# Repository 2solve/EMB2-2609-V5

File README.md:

# IC2S Extension Board EBM2 V5 — 6 entradas 4-20 mA

Placa de extensão da família IC2S (2Solve), código **IC2S-EBM2-2609-V5.0**. Seis entradas analógicas de 4-20 mA
para a Universal Baseboard; **substituição directa da EBM2 V4.1** (contorno 60 × 60 mm, furação e pinagem de
`P1`/`P2` congelados). Projecto em **KiCad 10**.

## Estado (2026-09-28)

| Fase | Estado |
|---|---|
| F0/F1 — escopo e planeamento | fechadas |
| F2 — esquemático, diagrama, BOM preliminar, mapa de pinos | **Portão 1 aprovado** (pacote congelado em `Portao1_aprovado_2026-09-25`) |
| F3 — layout | contorno e placement inicial feitos (DRC 0, paridade 0); falta o Portão 3 e o roteamento |

**Alteração posterior ao Portão 1 (2026-09-28)**, trazida da revisão da EBM7 V2.3: ramo único de 24 V (saem F1, D3 e
R3), 100 nF a 50 V fora do 24 V e um só MPN de 1 µF. Detalhe em
`Documentos_…/00-Especificações_Técnicas_…/alteracoes_reuniao_2026-09-28.md` e na folha 2, notas 3, 11, 13 e 14. Também a 28-09: **U5 MCP1824ST (SOT-223) → MCP1824T-3302E/OT (SOT-23-5)**, o mesmo MPN do U4; C10 (entrada) 1 µF → 10 µF 1206, o datasheet pede 1-10 µF
(`alteracao_LDO_3V3_lado_PLC_2026-09-28.md`). O
pacote congelado do Portão 1 não foi tocado; a BOM preliminar foi regenerada (42 linhas, 123 peças montadas).

## Organização (modelo de pastas de Produtos)

```
Desenvolvimento_IC2S-EBM2-2609-V5.0/
  Arquivos_Fabricação_IC2S-EBM2-2609-V5.0/
    00-Gerbers_…            (vazio até à F3)
    01-BOM_List_…           BOM preliminar (.md/.csv) e respostas cruas da API Mouser (2026-09-25)
    02-Pick-and-Place_…     (vazio até à F3)
    03-Stencil_…            (vazio até à F3)
  Documentos_IC2S-EBM2-2609-V5.0/
    00-Especificações_Técnicas_…   escopo, intenção, planeamento, relatórios, verificações da F2, Portão 1, F3
    01-Esquemáticos_…              PDF de revisão da F2 (esquemático + diagrama + mapa de pinos), PNG e SVG por folha
    02-Pinout_…                    mapa de pinos de P1/P2/U6/U7 e regras para o firmware
    03-Diagrama_Blocos_…           diagrama de blocos (SVG)
  Projeto_IC2S-EBM2-2609-V5.0/
    IC2S_Extension_Board-EBM2_V5.kicad_pro/.kicad_sch/.kicad_pcb e as 7 folhas
    symbols/, footprints/   bibliotecas próprias do projecto (sym-lib-table e fp-lib-table relativas)
    Ferramentas/            scripts Python de geração e verificação (ERC, netlist contra a intenção, BOM, PDF, F3)
    Documentos_de_Referência-IC2S-EBM2-2609-V5.0/   lista dos datasheets usados (nome e md5)
```

## O que não está neste repositório, e porquê

- **Datasheets dos fabricantes**: não se redistribuem num repositório público. `LISTA_datasheets.md` dá o nome e o
  md5 de cada ficheiro usado.
- Backups intermédios (`.antes_*`), netlists e relatórios ERC de passos intermédios, estado local do KiCad
  (`.kicad_prl`, `.history`).
- Ficheiros da V4.1 (Gerbers de origem usados para conferir o contorno): são de outro produto.

## Notas

- Os ficheiros KiCad mantêm o nome `IC2S_Extension_Board-EBM2_V5`: renomear o projecto partiria as instâncias
  dos símbolos nas folhas.
- Referências R1, R2… desde 2026-09-25; uma referência de três dígitos num documento é da numeração antiga
  (tabela em `tabela_correspondencia_refs_EBM2_V5.md`).
- Os scripts em `Ferramentas/` usam os caminhos locais de desenvolvimento (`C:\hw\hw-ebm2-v5`); a consulta à
  Mouser lê a chave de `MOUSER_API_KEY` e nunca a grava.

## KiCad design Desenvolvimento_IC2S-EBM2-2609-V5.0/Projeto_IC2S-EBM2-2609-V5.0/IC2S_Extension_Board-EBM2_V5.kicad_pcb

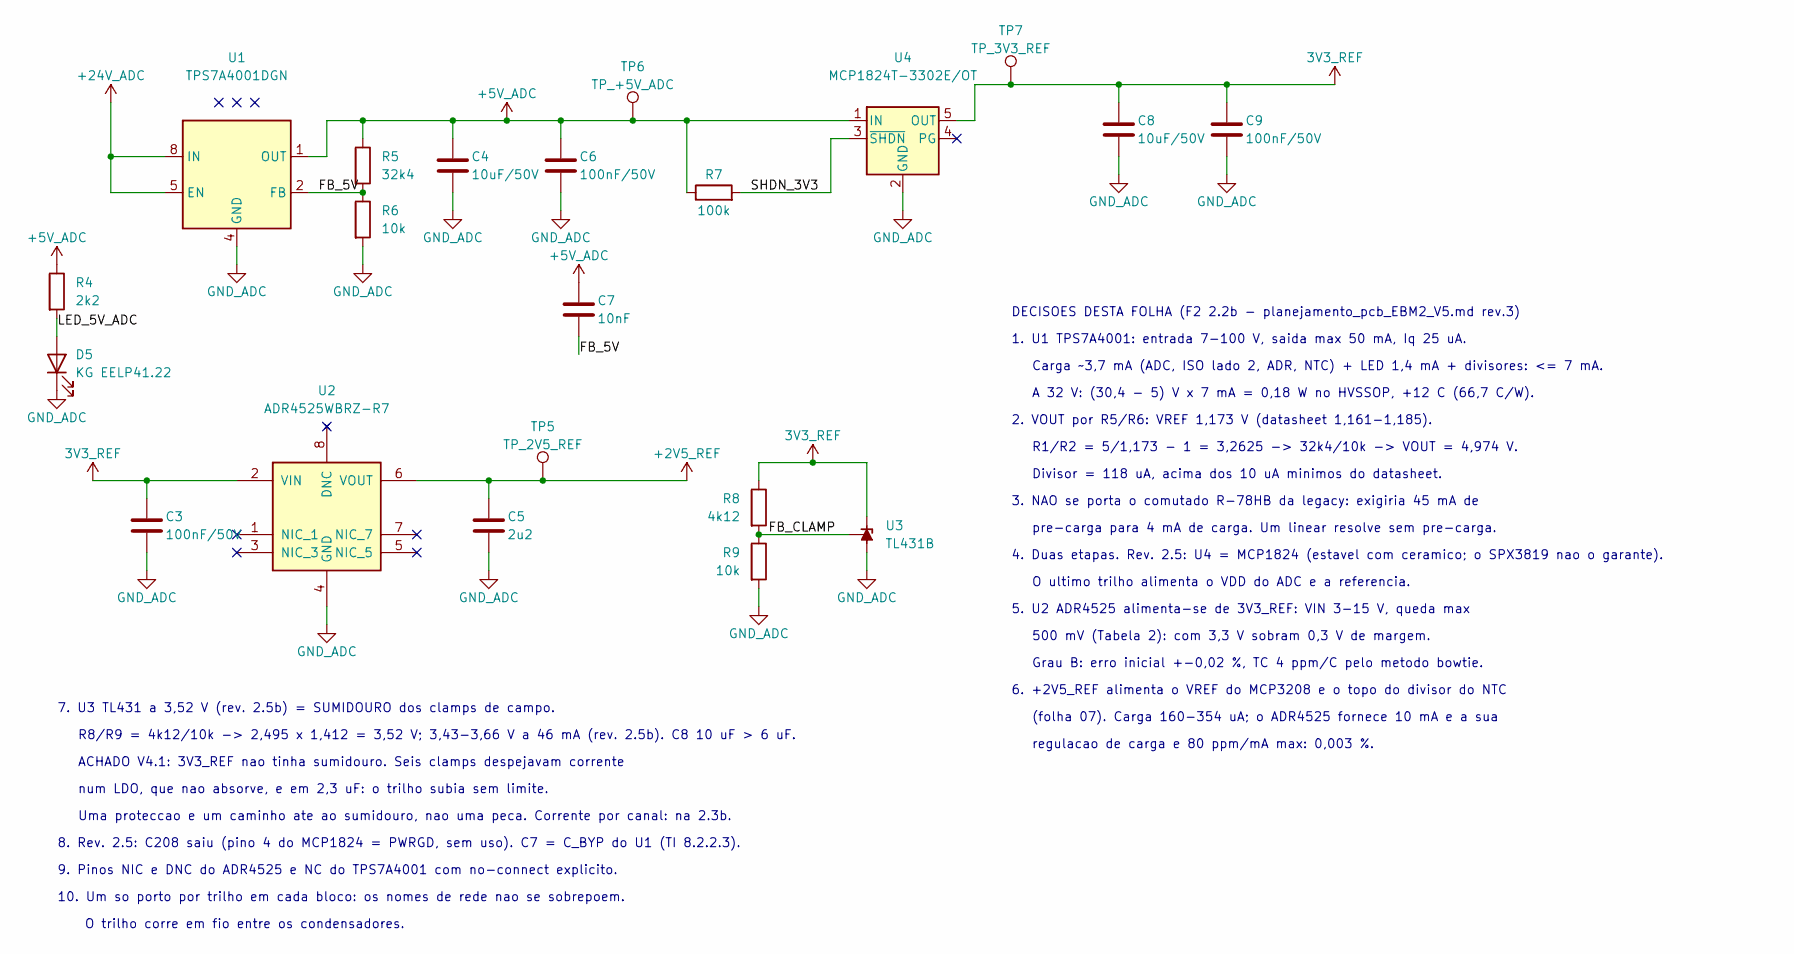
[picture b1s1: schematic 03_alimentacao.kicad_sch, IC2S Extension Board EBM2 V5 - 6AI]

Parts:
C3, C6, C9: 100nF/50V; 0603C; MPN C1608X7R1H104K080AA
C4, C8: 10uF/50V; C_1206_3216Metric; MPN C3216X5R1H106K160AB
C5: 2u2; 0603C; MPN C1608X5R1E225K080AB
C7: 10nF; 0603C; MPN GCM188R71H103KA37J
D5: KG EELP41.22; 0603LED; MPN KG EELP41.22-PHRH-35-A8J8-20-R18
R4: 2k2; 0603R; MPN RC0603FR-072K2L
R5: 32k4; 0603R; MPN RC0603FR-0732K4L
R6, R9: 10k; 0603R; MPN RC0603FR-0710KL
R7: 100k; 0603R; MPN RC0603FR-07100KL
R8: 4k12; 0603R; MPN RC0603FR-074K12L
TP5: TP_2V5_REF; TestPad_Via
TP6: TP_+5V_ADC; TestPad_Via
TP7: TP_3V3_REF; TestPad_Via
U1: TPS7A4001DGN; HVSSOP-8-1EP; MPN TPS7A4001DGNR
U2: ADR4525WBRZ-R7; SOIC8; MPN ADR4525WBRZ-R7
U3: TL431B; SOT23-3; MPN TL431BQDBZR
U4: MCP1824T-3302E/OT; SOT-23-5; MPN MCP1824T-3302E/OT

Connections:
3V3_REF: C3.1, C8.1, C9.1, R8.1, TP7.1, U2.2 (VIN), U3.1 (K), U4.5 (OUT); also elsewhere on the board
+2V5_REF: C5.1, TP5.1, U2.6 (VOUT); also elsewhere on the board
+5V_ADC: C4.1, C6.1, C7.1, R4.1, R5.1, R7.1, TP6.1, U1.1 (OUT), U4.1 (IN)
+24V_ADC: U1.5 (EN), U1.8 (IN); also elsewhere on the board
/3 Alimentacao/FB_5V: C7.2, R5.2, R6.1, U1.2 (FB)
/3 Alimentacao/FB_CLAMP: R8.2, R9.1, U3.2 (REF)
/3 Alimentacao/LED_5V_ADC: D5.2 (A), R4.2
/3 Alimentacao/SHDN_3V3: R7.2, U4.3 (~SHDN)
GND_ADC: C3.2, C4.2, C5.2, C6.2, C8.2, C9.2, D5.1 (K), R6.2, R9.2, U1.4 (GND), U1.9 (PAD), U2.4 (GND), U3.3 (A), U4.2 (GND); also elsewhere on the board

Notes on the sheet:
5. U2 ADR4525 alimenta-se de 3V3_REF: VIN 3-15 V, queda max
R1/R2 = 5/1,173 - 1 = 3,2625 -> 32k4/10k -> VOUT = 4,974 V.
1. U1 TPS7A4001: entrada 7-100 V, saida max 50 mA, Iq 25 uA.
Carga ~3,7 mA (ADC, ISO lado 2, ADR, NTC) + LED 1,4 mA + divisores: <= 7 mA.
Divisor = 118 uA, acima dos 10 uA minimos do datasheet.
10. Um so porto por trilho em cada bloco: os nomes de rede nao se sobrepoem.
7. U3 TL431 a 3,52 V (rev. 2.5b) = SUMIDOURO dos clamps de campo.
A 32 V: (30,4 - 5) V x 7 mA = 0,18 W no HVSSOP, +12 C (66,7 C/W).
regulacao de carga e 80 ppm/mA max: 0,003 %.
4. Duas etapas. Rev. 2.5: U4 = MCP1824 (estavel com ceramico; o SPX3819 nao o garante).
(folha 07). Carga 160-354 uA; o ADR4525 fornece 10 mA e a sua
pre-carga para 4 mA de carga. Um linear resolve sem pre-carga.
num LDO, que nao absorve, e em 2,3 uF: o trilho subia sem limite.
6. +2V5_REF alimenta o VREF do MCP3208 e o topo do divisor do NTC
Grau B: erro inicial +-0,02 %, TC 4 ppm/C pelo metodo bowtie.
O trilho corre em fio entre os condensadores.
Uma proteccao e um caminho ate ao sumidouro, nao uma peca. Corrente por canal: na 2.3b.
9. Pinos NIC e DNC do ADR4525 e NC do TPS7A4001 com no-connect explicito.
ACHADO V4.1: 3V3_REF nao tinha sumidouro. Seis clamps despejavam corrente
3. NAO se porta o comutado R-78HB da legacy: exigiria 45 mA de
R8/R9 = 4k12/10k -> 2,495 x 1,412 = 3,52 V; 3,43-3,66 V a 46 mA (rev. 2.5b). C8 10 uF > 6 uF.
500 mV (Tabela 2): com 3,3 V sobram 0,3 V de margem.
O ultimo trilho alimenta o VDD do ADC e a referencia.
2. VOUT por R5/R6: VREF 1,173 V (datasheet 1,161-1,185).
DECISOES DESTA FOLHA (F2 2.2b - planejamento_pcb_EBM2_V5.md rev.3)
8. Rev. 2.5: C208 saiu (pino 4 do MCP1824 = PWRGD, sem uso). C7 = C_BYP do U1 (TI 8.2.2.3).

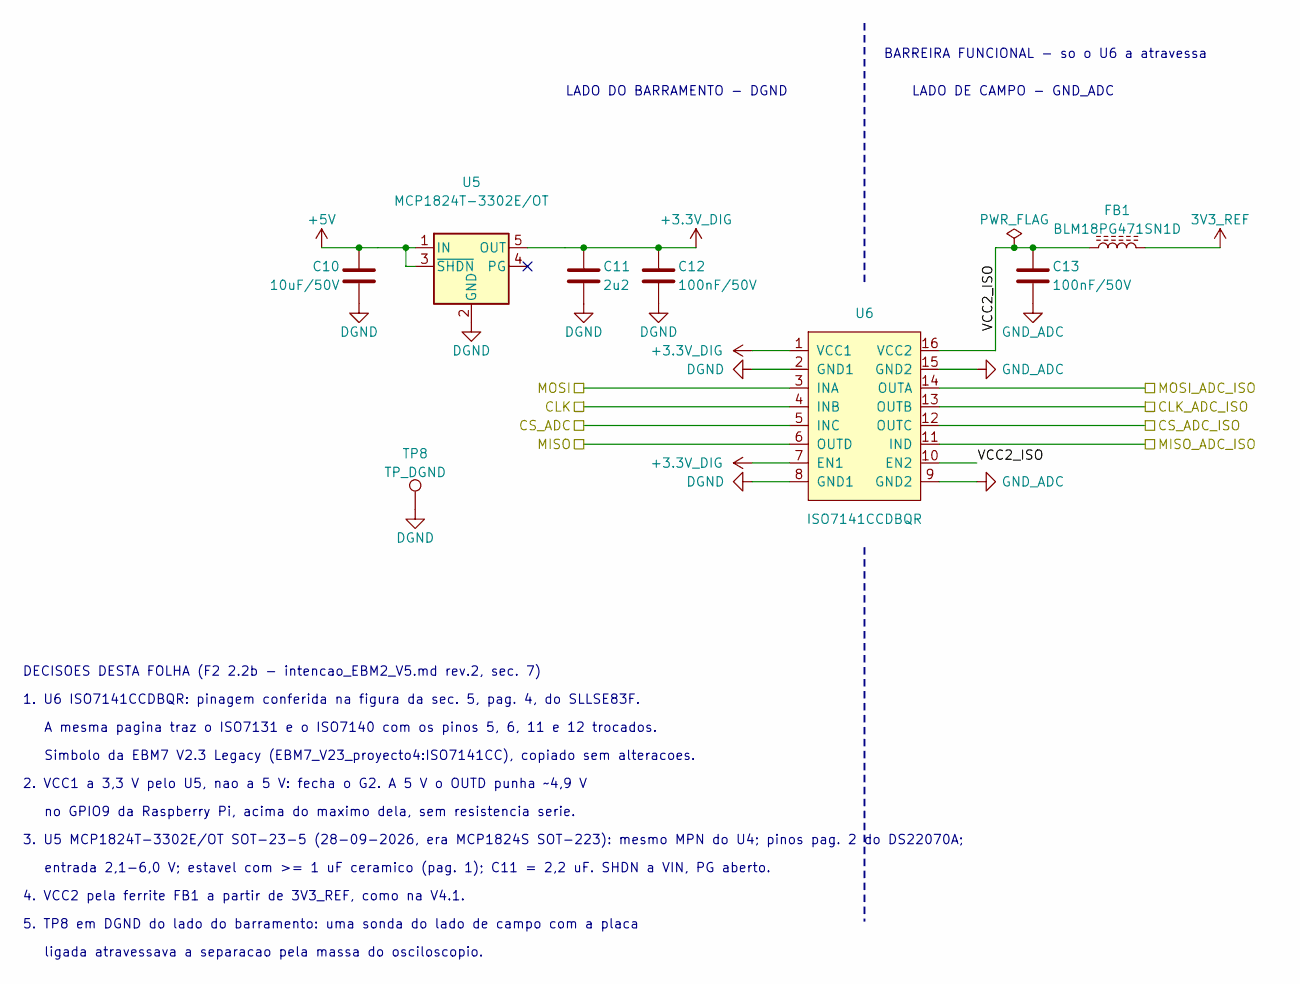
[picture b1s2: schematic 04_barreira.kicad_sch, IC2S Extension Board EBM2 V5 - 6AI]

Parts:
C10: 10uF/50V; C_1206_3216Metric; MPN C3216X5R1H106K160AB
C11: 2u2; 0603C; MPN C1608X5R1E225K080AB
C12, C13: 100nF/50V; 0603C; MPN C1608X7R1H104K080AA
FB1: BLM18PG471SN1D; 0603FB; MPN BLM18PG471SN1D
TP8: TP_DGND; TestPad_Via
U5: MCP1824T-3302E/OT; SOT-23-5; MPN MCP1824T-3302E/OT
U6: ISO7141CCDBQR; SSOP16-4.9x3.9mm; MPN ISO7141CCDBQR

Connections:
3V3_REF: FB1.2; also elsewhere on the board
+3.3V_DIG: C11.1, C12.1, U5.5 (OUT), U6.1 (VCC1), U6.7 (EN1)
+5V: C10.1, U5.1 (IN), U5.3 (~SHDN); also elsewhere on the board
/1 Conectores/CLK: U6.4 (INB); also elsewhere on the board
/1 Conectores/CS_ADC: U6.5 (INC); also elsewhere on the board
/1 Conectores/MISO: U6.6 (OUTD); also elsewhere on the board
/1 Conectores/MOSI: U6.3 (INA); also elsewhere on the board
/4 Barreira digital/CLK_ADC_ISO: U6.13 (OUTB); also elsewhere on the board
/4 Barreira digital/CS_ADC_ISO: U6.12 (OUTC); also elsewhere on the board
/4 Barreira digital/MISO_ADC_ISO: U6.11 (IND); also elsewhere on the board
/4 Barreira digital/MOSI_ADC_ISO: U6.14 (OUTA); also elsewhere on the board
/4 Barreira digital/VCC2_ISO: C13.1, FB1.1, U6.10 (EN2), U6.16 (VCC2)
DGND: C10.2, C11.2, C12.2, TP8.1, U5.2 (GND), U6.2 (GND1), U6.8 (GND1); also elsewhere on the board
GND_ADC: C13.2, U6.9 (GND2), U6.15 (GND2); also elsewhere on the board

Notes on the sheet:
BARREIRA FUNCIONAL - so o U6 a atravessa
LADO DO BARRAMENTO - DGND
LADO DE CAMPO - GND_ADC
DECISOES DESTA FOLHA (F2 2.2b - intencao_EBM2_V5.md rev.2, sec. 7)
1. U6 ISO7141CCDBQR: pinagem conferida na figura da sec. 5, pag. 4, do SLLSE83F.
A mesma pagina traz o ISO7131 e o ISO7140 com os pinos 5, 6, 11 e 12 trocados.
Simbolo da EBM7 V2.3 Legacy (EBM7_V23_proyecto4:ISO7141CC), copiado sem alteracoes.
2. VCC1 a 3,3 V pelo U5, nao a 5 V: fecha o G2. A 5 V o OUTD punha ~4,9 V
no GPIO9 da Raspberry Pi, acima do maximo dela, sem resistencia serie.
3. U5 MCP1824T-3302E/OT SOT-23-5 (28-09-2026, era MCP1824S SOT-223): mesmo MPN do U4; pinos pag. 2 do DS22070A;
entrada 2,1-6,0 V; estavel com >= 1 uF ceramico (pag. 1); C11 = 2,2 uF. SHDN a VIN, PG aberto.
4. VCC2 pela ferrite FB1 a partir de 3V3_REF, como na V4.1.
5. TP8 em DGND do lado do barramento: uma sonda do lado de campo com a placa
ligada atravessava a separacao pela massa do osciloscopio.

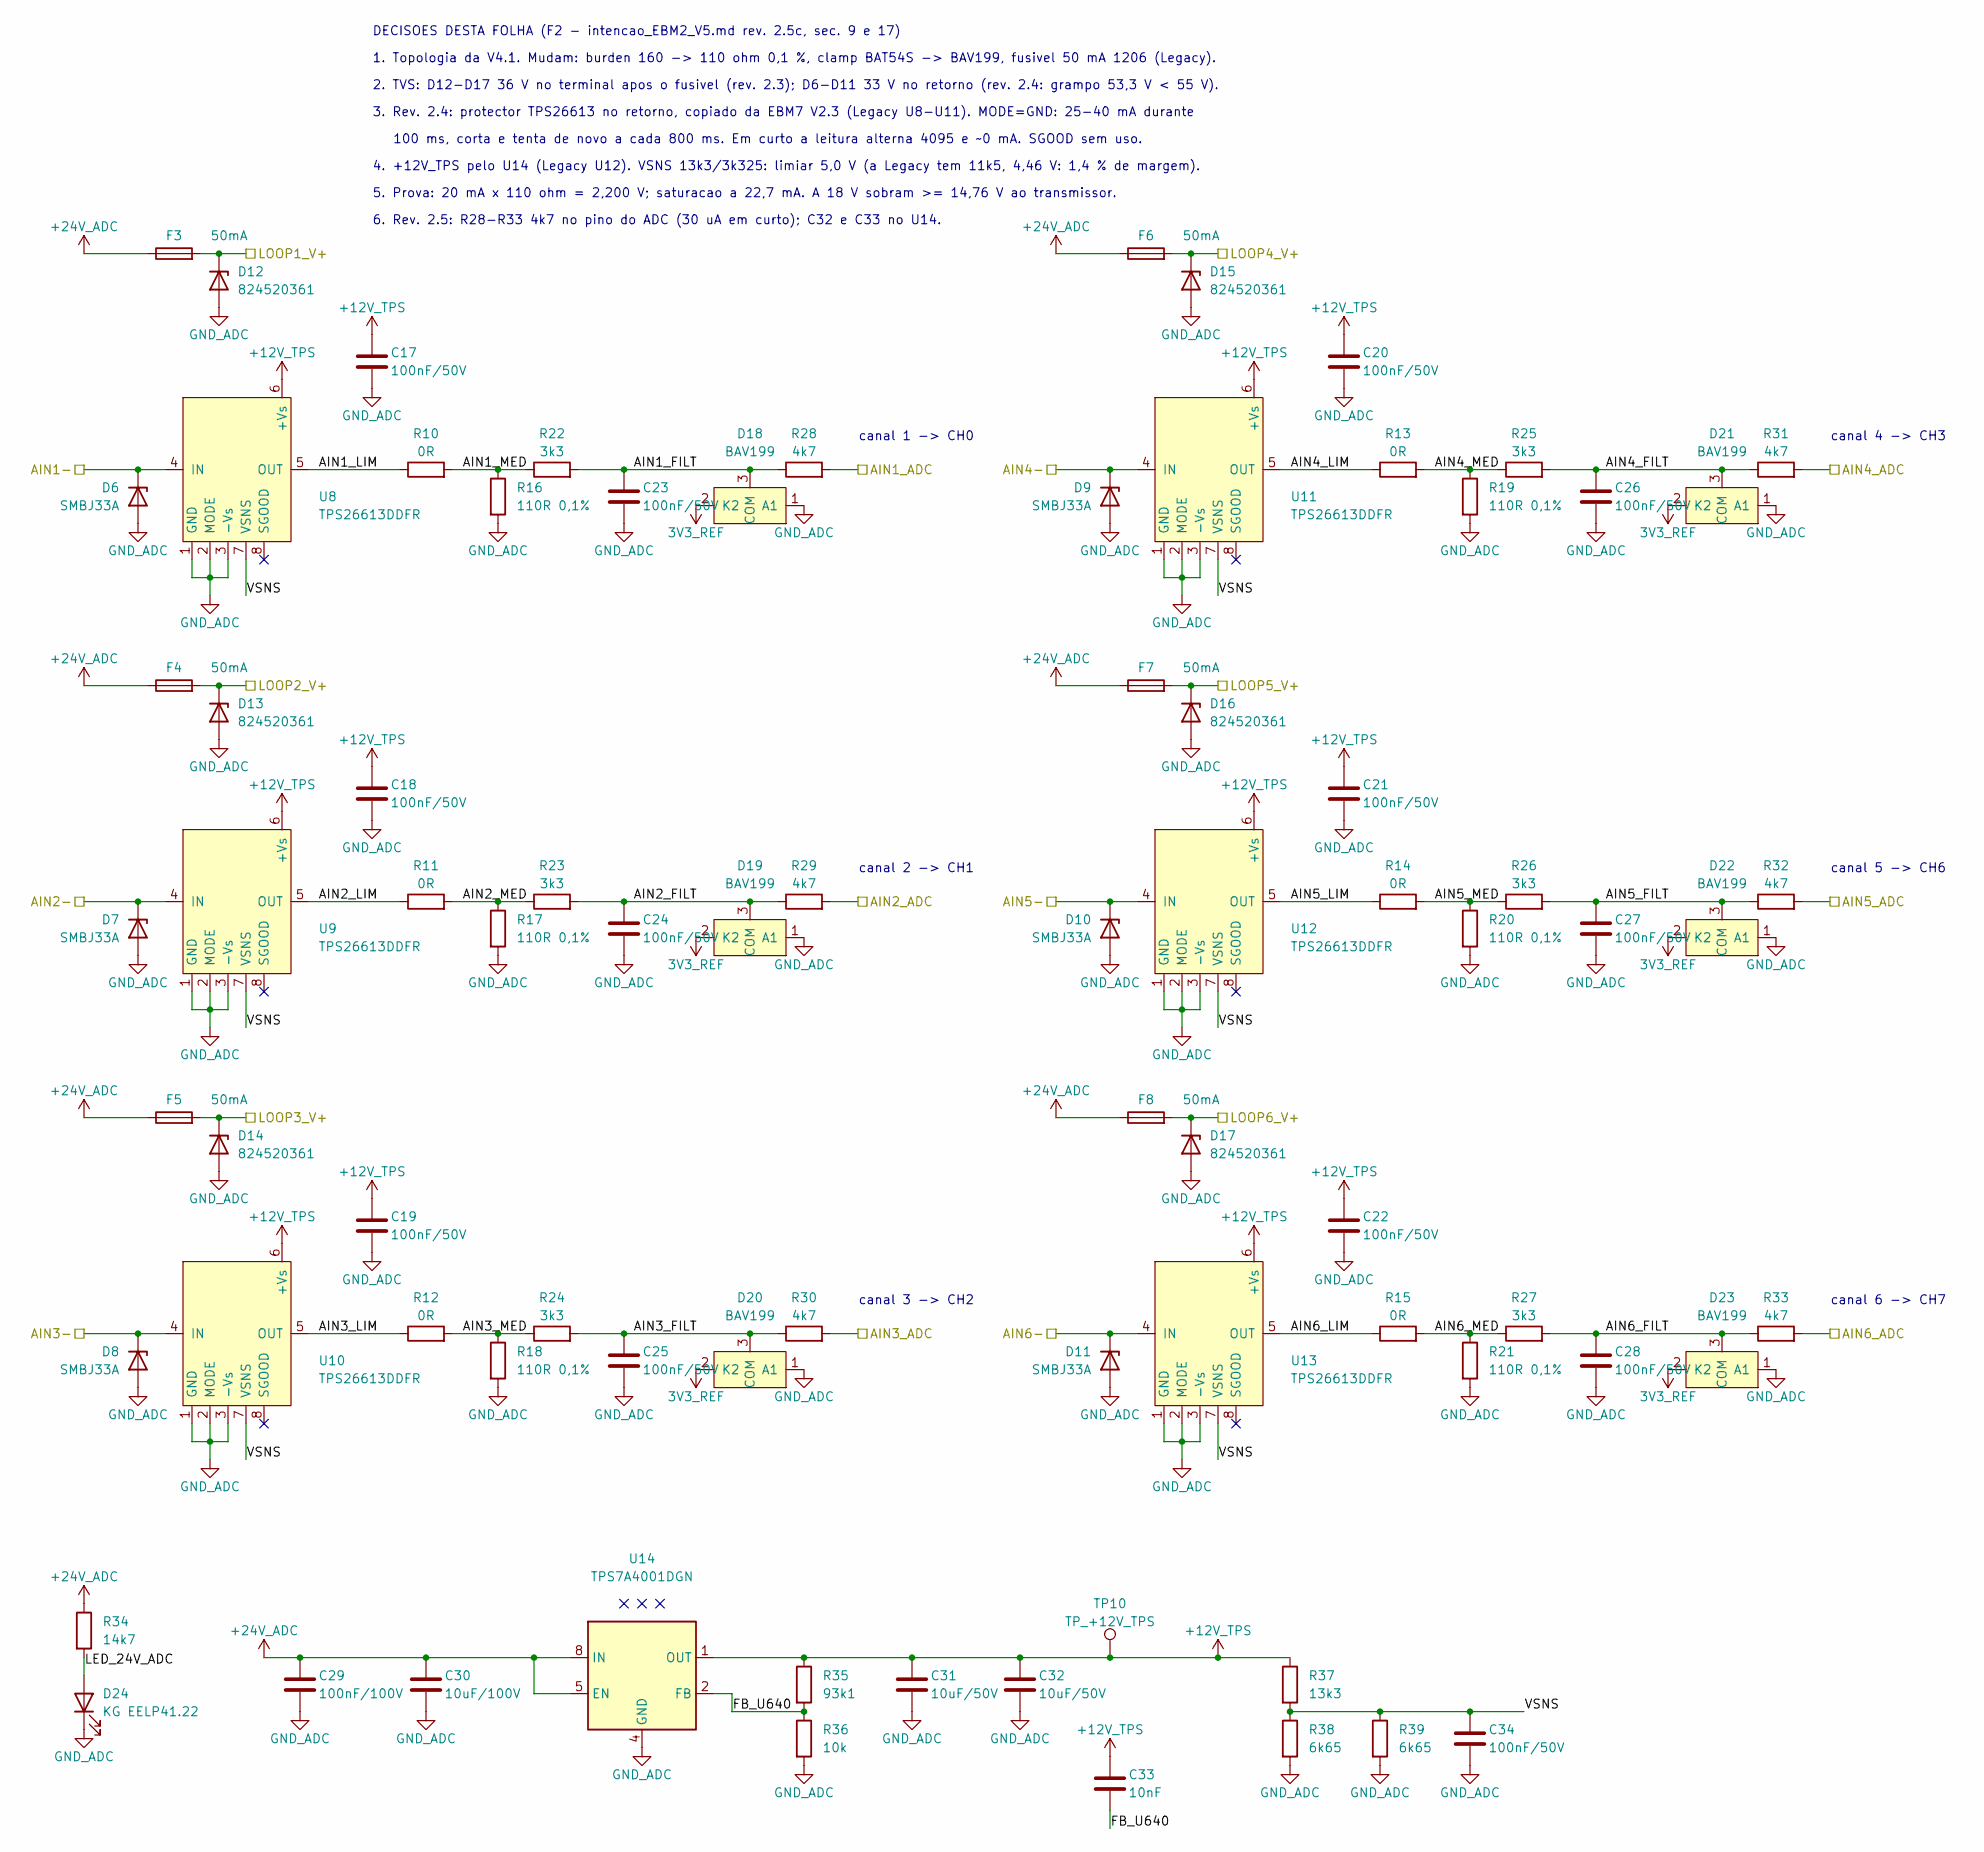
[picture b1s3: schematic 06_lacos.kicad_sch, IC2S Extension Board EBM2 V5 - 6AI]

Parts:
C17, C18, C19, C20, C21, C22, C23, C24, C25, C26, C27, C28, C34: 100nF/50V; 0603C; MPN C1608X7R1H104K080AA
C29: 100nF/100V; 0603C; MPN GRM188R72A104KA35D
C30: 10uF/100V; C_1210_3225Metric; MPN GRM32EC72A106ME05L
C31, C32: 10uF/50V; C_1206_3216Metric; MPN C3216X5R1H106K160AB
C33: 10nF; 0603C; MPN GCM188R71H103KA37J
D6, D7, D8, D9, D10, D11: SMBJ33A; DO-214AA; MPN SMBJ33A-13-F
D12, D13, D14, D15, D16, D17: 824520361; DO-214AA; MPN 824520361
D18, D19, D20, D21, D22, D23: BAV199; SOT23-3; MPN BAV199LT1G
D24: KG EELP41.22; 0603LED; MPN KG EELP41.22-PHRH-35-A8J8-20-R18
F3, F4, F5, F6, F7, F8: 50mA; 1206F; MPN 3413.0002.22
R10, R11, R12, R13, R14, R15: 0R; 0603R; MPN RC0603JR-070RL
R16, R17, R18, R19, R20, R21: 110R 0,1%; 1206R; MPN ERA8AEB111V
R22, R23, R24, R25, R26, R27: 3k3; 0603R; MPN RC0603FR-073K3L
R28, R29, R30, R31, R32, R33: 4k7; 0603R; MPN RC0603FR-074K7L
R34: 14k7; 0603R; MPN ERJ-3EKF1472V
R35: 93k1; 0603R; MPN RMCF0603FT93K1
R36: 10k; 0603R; MPN RC0603FR-0710KL
R37: 13k3; 0603R; MPN RC0603FR-0713K3L
R38, R39: 6k65; 0603R; MPN RC0603FR-076K65L
TP10: TP_+12V_TPS; TestPad_Via
U8, U9, U10, U11, U12, U13: TPS26613DDFR; SOT-23-8; MPN TPS26613DDFR
U14: TPS7A4001DGN; HVSSOP-8-1EP; MPN TPS7A4001DGNR

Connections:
3V3_REF: D18.2 (K2), D19.2 (K2), D20.2 (K2), D21.2 (K2), D22.2 (K2), D23.2 (K2); also elsewhere on the board
+12V_TPS: C17.1, C18.1, C19.1, C20.1, C21.1, C22.1, C31.1, C32.1, C33.1, R35.1, R37.1, TP10.1, U8.6 (+Vs), U9.6 (+Vs), U10.6 (+Vs), U11.6 (+Vs), U12.6 (+Vs), U13.6 (+Vs), U14.1 (OUT)
+24V_ADC: C29.1, C30.1, F3.1, F4.1, F5.1, F6.1, F7.1, F8.1, R34.1, U14.5 (EN), U14.8 (IN); also elsewhere on the board
/1 Conectores/AIN1-: D6.1 (K), U8.4 (IN); also elsewhere on the board
/1 Conectores/AIN2-: D7.1 (K), U9.4 (IN); also elsewhere on the board
/1 Conectores/AIN3-: D8.1 (K), U10.4 (IN); also elsewhere on the board
/1 Conectores/AIN4-: D9.1 (K), U11.4 (IN); also elsewhere on the board
/1 Conectores/AIN5-: D10.1 (K), U12.4 (IN); also elsewhere on the board
/1 Conectores/AIN6-: D11.1 (K), U13.4 (IN); also elsewhere on the board
/1 Conectores/LOOP1_V+: D12.1 (K), F3.2; also elsewhere on the board
/1 Conectores/LOOP2_V+: D13.1 (K), F4.2; also elsewhere on the board
/1 Conectores/LOOP3_V+: D14.1 (K), F5.2; also elsewhere on the board
/1 Conectores/LOOP4_V+: D15.1 (K), F6.2; also elsewhere on the board
/1 Conectores/LOOP5_V+: D16.1 (K), F7.2; also elsewhere on the board
/1 Conectores/LOOP6_V+: D17.1 (K), F8.2; also elsewhere on the board
/5 ADC/AIN1_ADC: R28.2; also elsewhere on the board
/5 ADC/AIN2_ADC: R29.2; also elsewhere on the board
/5 ADC/AIN3_ADC: R30.2; also elsewhere on the board
/5 ADC/AIN4_ADC: R31.2; also elsewhere on the board
/5 ADC/AIN5_ADC: R32.2; also elsewhere on the board
/5 ADC/AIN6_ADC: R33.2; also elsewhere on the board
/6 Lacos/AIN1_FILT: C23.1, D18.3 (COM), R22.2, R28.1
/6 Lacos/AIN1_LIM: R10.1, U8.5 (OUT)
/6 Lacos/AIN1_MED: R10.2, R16.1, R22.1
/6 Lacos/AIN2_FILT: C24.1, D19.3 (COM), R23.2, R29.1
/6 Lacos/AIN2_LIM: R11.1, U9.5 (OUT)
/6 Lacos/AIN2_MED: R11.2, R17.1, R23.1
/6 Lacos/AIN3_FILT: C25.1, D20.3 (COM), R24.2, R30.1
/6 Lacos/AIN3_LIM: R12.1, U10.5 (OUT)
/6 Lacos/AIN3_MED: R12.2, R18.1, R24.1
/6 Lacos/AIN4_FILT: C26.1, D21.3 (COM), R25.2, R31.1
/6 Lacos/AIN4_LIM: R13.1, U11.5 (OUT)
/6 Lacos/AIN4_MED: R13.2, R19.1, R25.1
/6 Lacos/AIN5_FILT: C27.1, D22.3 (COM), R26.2, R32.1
/6 Lacos/AIN5_LIM: R14.1, U12.5 (OUT)
/6 Lacos/AIN5_MED: R14.2, R20.1, R26.1
/6 Lacos/AIN6_FILT: C28.1, D23.3 (COM), R27.2, R33.1
/6 Lacos/AIN6_LIM: R15.1, U13.5 (OUT)
/6 Lacos/AIN6_MED: R15.2, R21.1, R27.1
/6 Lacos/FB_U640: C33.2, R35.2, R36.1, U14.2 (FB)
/6 Lacos/LED_24V_ADC: D24.2 (A), R34.2
/6 Lacos/VSNS: C34.1, R37.2, R38.1, R39.1, U8.7 (VSNS), U9.7 (VSNS), U10.7 (VSNS), U11.7 (VSNS), U12.7 (VSNS), U13.7 (VSNS)
GND_ADC: C17.2, C18.2, C19.2, C20.2, C21.2, C22.2, C23.2, C24.2, C25.2, C26.2, C27.2, C28.2, C29.2, C30.2, C31.2, C32.2, C34.2, D6.2 (A), D7.2 (A), D8.2 (A), D9.2 (A), D10.2 (A), D11.2 (A), D12.2 (A), D13.2 (A), D14.2 (A), D15.2 (A), D16.2 (A), D17.2 (A), D18.1 (A1), D19.1 (A1), D20.1 (A1), D21.1 (A1), D22.1 (A1), D23.1 (A1), D24.1 (K), R16.2, R17.2, R18.2, R19.2, R20.2, R21.2, R36.2, R38.2, R39.2, U8.1 (GND), U8.2 (MODE), U8.3 (-Vs), U9.1 (GND), U9.2 (MODE), U9.3 (-Vs), U10.1 (GND), U10.2 (MODE), U10.3 (-Vs), U11.1 (GND), U11.2 (MODE), U11.3 (-Vs), U12.1 (GND), U12.2 (MODE), U12.3 (-Vs), U13.1 (GND), U13.2 (MODE), U13.3 (-Vs), U14.4 (GND), U14.9 (PAD); also elsewhere on the board

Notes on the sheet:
canal 1 -> CH0
canal 2 -> CH1
canal 3 -> CH2
canal 4 -> CH3
canal 5 -> CH6
canal 6 -> CH7
DECISOES DESTA FOLHA (F2 - intencao_EBM2_V5.md rev. 2.5c, sec. 9 e 17)
1. Topologia da V4.1. Mudam: burden 160 -> 110 ohm 0,1 %, clamp BAT54S -> BAV199, fusivel 50 mA 1206 (Legacy).
2. TVS: D12-D17 36 V no terminal apos o fusivel (rev. 2.3); D6-D11 33 V no retorno (rev. 2.4: grampo 53,3 V < 55 V).
3. Rev. 2.4: protector TPS26613 no retorno, copiado da EBM7 V2.3 (Legacy U8-U11). MODE=GND: 25-40 mA durante
100 ms, corta e tenta de novo a cada 800 ms. Em curto a leitura alterna 4095 e ~0 mA. SGOOD sem uso.
4. +12V_TPS pelo U14 (Legacy U12). VSNS 13k3/3k325: limiar 5,0 V (a Legacy tem 11k5, 4,46 V: 1,4 % de margem).
5. Prova: 20 mA x 110 ohm = 2,200 V; saturacao a 22,7 mA. A 18 V sobram >= 14,76 V ao transmissor.
6. Rev. 2.5: R28-R33 4k7 no pino do ADC (30 uA em curto); C32 e C33 no U14.

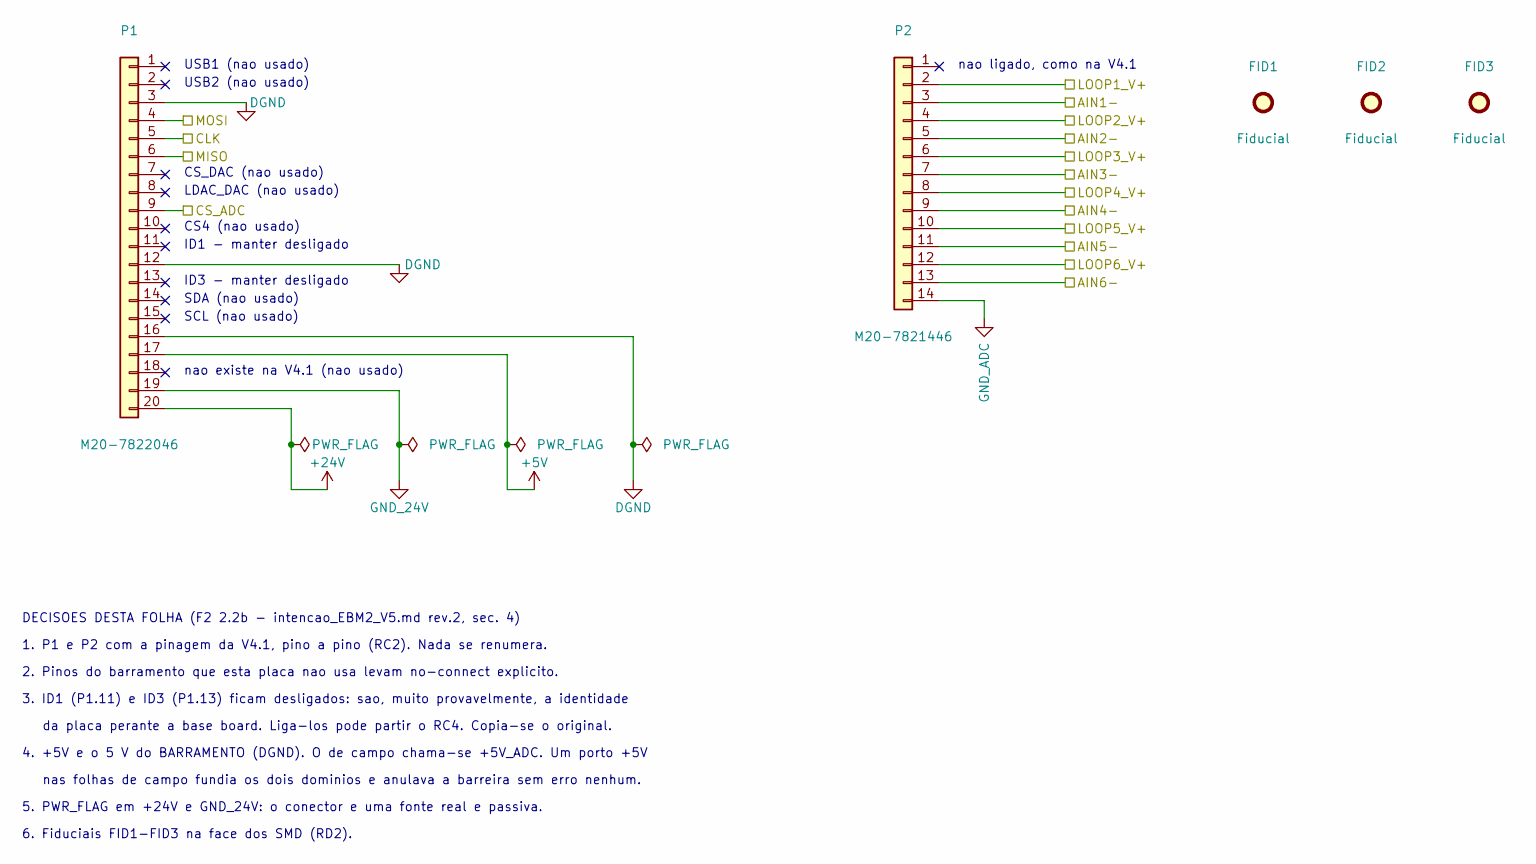
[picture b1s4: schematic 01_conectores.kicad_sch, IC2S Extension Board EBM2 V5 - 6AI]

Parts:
FID1, FID2, FID3: Fiducial; Fiducial_Point_Top-Bot
P1: M20-7822046; HDR1X20_FEMALE; MPN M20-7822046
P2: M20-7821446; HDR1X14_FEMALE; MPN M20-7821446

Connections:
+5V: P1.17; also elsewhere on the board
+24V: P1.20; also elsewhere on the board
/1 Conectores/AIN1-: P2.3; also elsewhere on the board
/1 Conectores/AIN2-: P2.5; also elsewhere on the board
/1 Conectores/AIN3-: P2.7; also elsewhere on the board
/1 Conectores/AIN4-: P2.9; also elsewhere on the board
/1 Conectores/AIN5-: P2.11; also elsewhere on the board
/1 Conectores/AIN6-: P2.13; also elsewhere on the board
/1 Conectores/CLK: P1.5; also elsewhere on the board
/1 Conectores/CS_ADC: P1.9; also elsewhere on the board
/1 Conectores/LOOP1_V+: P2.2; also elsewhere on the board
/1 Conectores/LOOP2_V+: P2.4; also elsewhere on the board
/1 Conectores/LOOP3_V+: P2.6; also elsewhere on the board
/1 Conectores/LOOP4_V+: P2.8; also elsewhere on the board
/1 Conectores/LOOP5_V+: P2.10; also elsewhere on the board
/1 Conectores/LOOP6_V+: P2.12; also elsewhere on the board
/1 Conectores/MISO: P1.6; also elsewhere on the board
/1 Conectores/MOSI: P1.4; also elsewhere on the board
DGND: P1.3, P1.12, P1.16; also elsewhere on the board
GND_24V: P1.19; also elsewhere on the board
GND_ADC: P2.14; also elsewhere on the board

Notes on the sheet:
nao ligado, como na V4.1
6. Fiduciais FID1-FID3 na face dos SMD (RD2).
USB2 (nao usado)
4. +5V e o 5 V do BARRAMENTO (DGND). O de campo chama-se +5V_ADC. Um porto +5V
SCL (nao usado)
CS_DAC (nao usado)
nao existe na V4.1 (nao usado)
5. PWR_FLAG em +24V e GND_24V: o conector e uma fonte real e passiva.
3. ID1 (P1.11) e ID3 (P1.13) ficam desligados: sao, muito provavelmente, a identidade
USB1 (nao usado)
LDAC_DAC (nao usado)
ID1 - manter desligado
da placa perante a base board. Liga-los pode partir o RC4. Copia-se o original.
ID3 - manter desligado
DECISOES DESTA FOLHA (F2 2.2b - intencao_EBM2_V5.md rev.2, sec. 4)
nas folhas de campo fundia os dois dominios e anulava a barreira sem erro nenhum.
1. P1 e P2 com a pinagem da V4.1, pino a pino (RC2). Nada se renumera.
CS4 (nao usado)
SDA (nao usado)
2. Pinos do barramento que esta placa nao usa levam no-connect explicito.

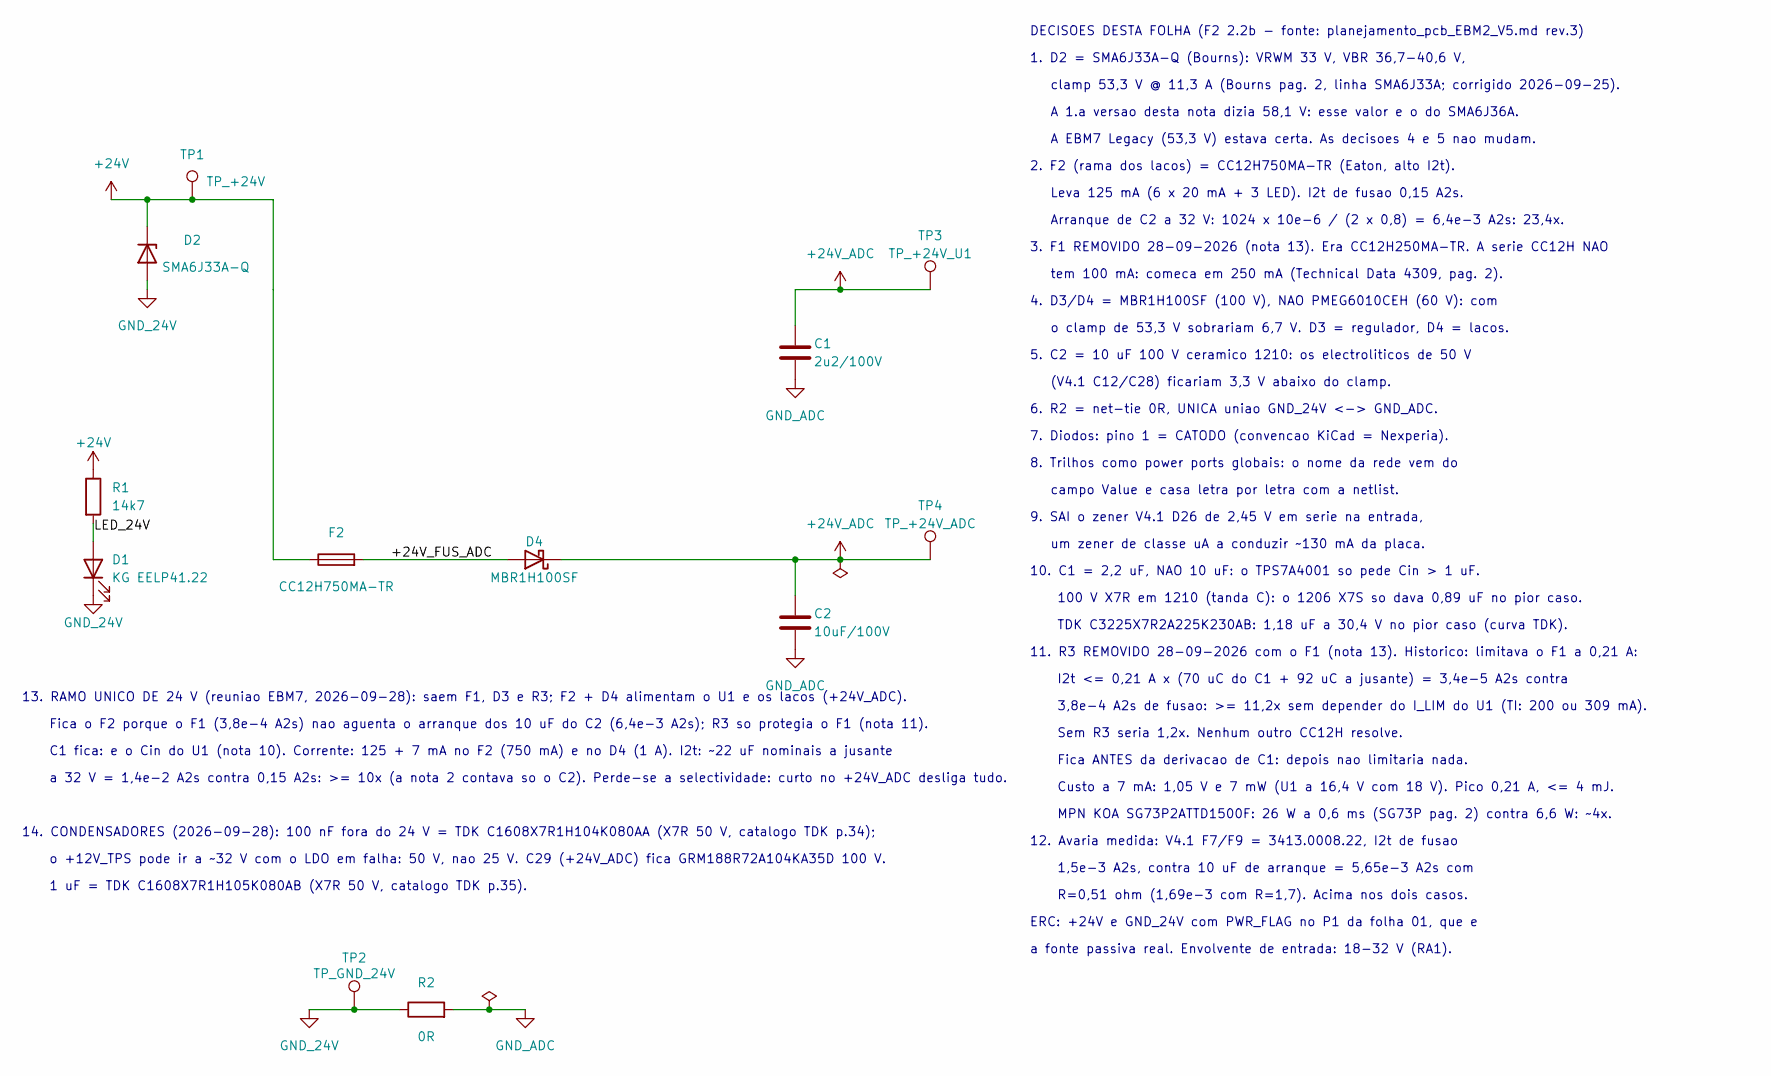
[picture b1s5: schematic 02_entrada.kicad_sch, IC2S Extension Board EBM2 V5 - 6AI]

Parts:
C1: 2u2/100V; C_1210_3225Metric; MPN C3225X7R2A225K230AB
C2: 10uF/100V; C_1210_3225Metric; MPN GRM32EC72A106ME05L
D1: KG EELP41.22; 0603LED; MPN KG EELP41.22-PHRH-35-A8J8-20-R18
D2: SMA6J33A-Q; DO-214; MPN SMA6J33A-Q
D4: MBR1H100SF; SOD123; MPN MBR1H100SFT3G
F2: CC12H750MA-TR; 1206F; MPN CC12H750MA-TR
R1: 14k7; 0603R; MPN ERJ-3EKF1472V
R2: 0R; 0603R; MPN RC0603JR-070RL
TP1: TP_+24V; TestPad_Via
TP2: TP_GND_24V; TestPad_Via
TP3: TP_+24V_U1; TestPad_Via
TP4: TP_+24V_ADC; TestPad_Via

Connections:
+24V: D2.1 (K), F2.1, R1.1, TP1.1; also elsewhere on the board
+24V_ADC: C1.1, C2.1, D4.1 (K), TP3.1, TP4.1; also elsewhere on the board
/2 Entrada/+24V_FUS_ADC: D4.2 (A), F2.2
/2 Entrada/LED_24V: D1.2 (A), R1.2
GND_24V: D1.1 (K), D2.2 (A), R2.1, TP2.1; also elsewhere on the board
GND_ADC: C1.2, C2.2, R2.2; also elsewhere on the board

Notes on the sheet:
Fica ANTES da derivacao de C1: depois nao limitaria nada.
TDK C3225X7R2A225K230AB: 1,18 uF a 30,4 V no pior caso (curva TDK).
Sem R3 seria 1,2x. Nenhum outro CC12H resolve.
5. C2 = 10 uF 100 V ceramico 1210: os electroliticos de 50 V
8. Trilhos como power ports globais: o nome da rede vem do
MPN KOA SG73P2ATTD1500F: 26 W a 0,6 ms (SG73P pag. 2) contra 6,6 W: ~4x.
A EBM7 Legacy (53,3 V) estava certa. As decisoes 4 e 5 nao mudam.
1,5e-3 A2s, contra 10 uF de arranque = 5,65e-3 A2s com
7. Diodos: pino 1 = CATODO (convencao KiCad = Nexperia).
A 1.a versao desta nota dizia 58,1 V: esse valor e o do SMA6J36A.
campo Value e casa letra por letra com a netlist.
Custo a 7 mA: 1,05 V e 7 mW (U1 a 16,4 V com 18 V). Pico 0,21 A, <= 4 mJ.
2. F2 (rama dos lacos) = CC12H750MA-TR (Eaton, alto I2t).
100 V X7R em 1210 (tanda C): o 1206 X7S so dava 0,89 uF no pior caso.
Arranque de C2 a 32 V: 1024 x 10e-6 / (2 x 0,8) = 6,4e-3 A2s: 23,4x.
a fonte passiva real. Envolvente de entrada: 18-32 V (RA1).
(V4.1 C12/C28) ficariam 3,3 V abaixo do clamp.
1. D2 = SMA6J33A-Q (Bourns): VRWM 33 V, VBR 36,7-40,6 V,
tem 100 mA: comeca em 250 mA (Technical Data 4309, pag. 2).
R=0,51 ohm (1,69e-3 com R=1,7). Acima nos dois casos.
um zener de classe uA a conduzir ~130 mA da placa.
12. Avaria medida: V4.1 F7/F9 = 3413.0008.22, I2t de fusao
11. R3 REMOVIDO 28-09-2026 com o F1 (nota 13). Historico: limitava o F1 a 0,21 A:
4. D3/D4 = MBR1H100SF (100 V), NAO PMEG6010CEH (60 V): com
ERC: +24V e GND_24V com PWR_FLAG no P1 da folha 01, que e
9. SAI o zener V4.1 D26 de 2,45 V em serie na entrada,
3,8e-4 A2s de fusao: >= 11,2x sem depender do I_LIM do U1 (TI: 200 ou 309 mA).
Leva 125 mA (6 x 20 mA + 3 LED). I2t de fusao 0,15 A2s.
o clamp de 53,3 V sobrariam 6,7 V. D3 = regulador, D4 = lacos.
clamp 53,3 V @ 11,3 A (Bourns pag. 2, linha SMA6J33A; corrigido 2026-09-25).
DECISOES DESTA FOLHA (F2 2.2b - fonte: planejamento_pcb_EBM2_V5.md rev.3)
I2t <= 0,21 A x (70 uC do C1 + 92 uC a jusante) = 3,4e-5 A2s contra
3. F1 REMOVIDO 28-09-2026 (nota 13). Era CC12H250MA-TR. A serie CC12H NAO
6. R2 = net-tie 0R, UNICA uniao GND_24V <-> GND_ADC.
10. C1 = 2,2 uF, NAO 10 uF: o TPS7A4001 so pede Cin > 1 uF.
13. RAMO UNICO DE 24 V (reuniao EBM7, 2026-09-28): saem F1, D3 e R3; F2 + D4 alimentam o U1 e os lacos (+24V_ADC).
Fica o F2 porque o F1 (3,8e-4 A2s) nao aguenta o arranque dos 10 uF do C2 (6,4e-3 A2s); R3 so protegia o F1 (nota 11).
C1 fica: e o Cin do U1 (nota 10). Corrente: 125 + 7 mA no F2 (750 mA) e no D4 (1 A). I2t: ~22 uF nominais a jusante
a 32 V = 1,4e-2 A2s contra 0,15 A2s: >= 10x (a nota 2 contava so o C2). Perde-se a selectividade: curto no +24V_ADC desliga tudo.
14. CONDENSADORES (2026-09-28): 100 nF fora do 24 V = TDK C1608X7R1H104K080AA (X7R 50 V, catalogo TDK p.34);

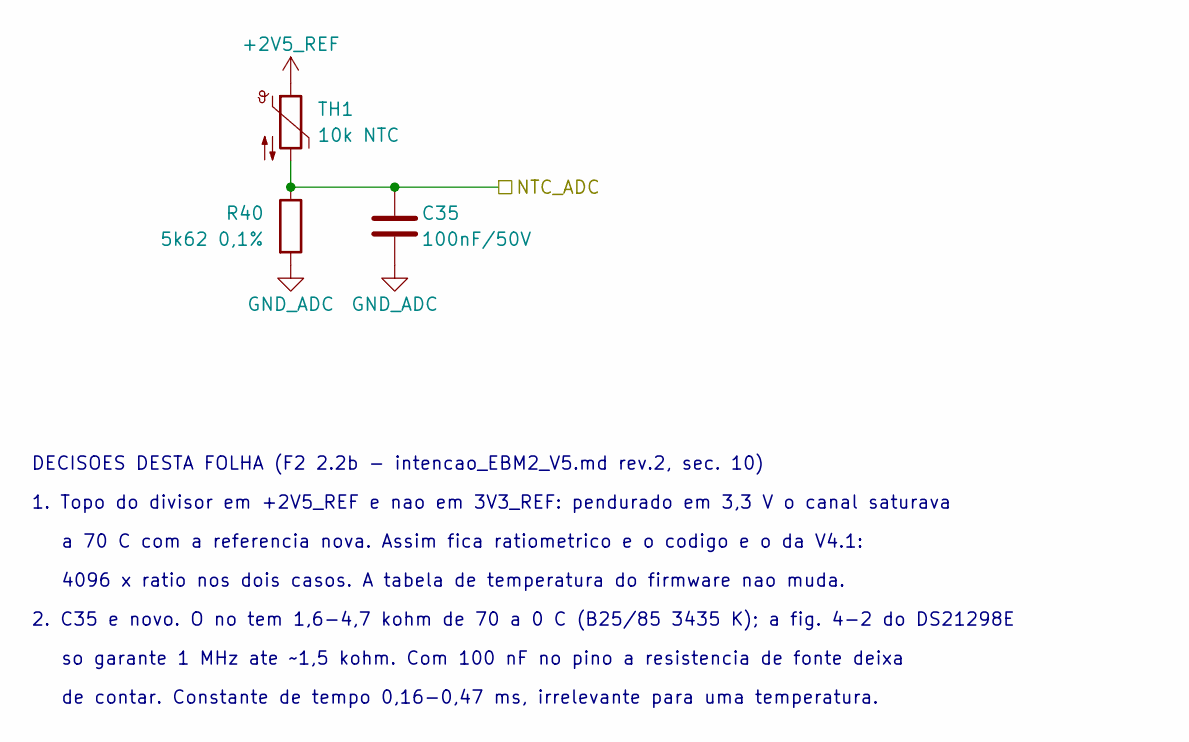
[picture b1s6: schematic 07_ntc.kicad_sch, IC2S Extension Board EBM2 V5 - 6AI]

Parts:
C35: 100nF/50V; 0603C; MPN C1608X7R1H104K080AA
R40: 5k62 0,1%; 0603R; MPN ERA3AEB5621V
TH1: 10k NTC; 0603R; MPN NTCS0603E3103JLT

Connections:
+2V5_REF: TH1.1; also elsewhere on the board
/5 ADC/NTC_ADC: C35.1, R40.1, TH1.2; also elsewhere on the board
GND_ADC: C35.2, R40.2; also elsewhere on the board

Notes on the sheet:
DECISOES DESTA FOLHA (F2 2.2b - intencao_EBM2_V5.md rev.2, sec. 10)
1. Topo do divisor em +2V5_REF e nao em 3V3_REF: pendurado em 3,3 V o canal saturava
a 70 C com a referencia nova. Assim fica ratiometrico e o codigo e o da V4.1:
4096 x ratio nos dois casos. A tabela de temperatura do firmware nao muda.
2. C35 e novo. O no tem 1,6-4,7 kohm de 70 a 0 C (B25/85 3435 K); a fig. 4-2 do DS21298E
so garante 1 MHz ate ~1,5 kohm. Com 100 nF no pino a resistencia de fonte deixa
de contar. Constante de tempo 0,16-0,47 ms, irrelevante para uma temperatura.

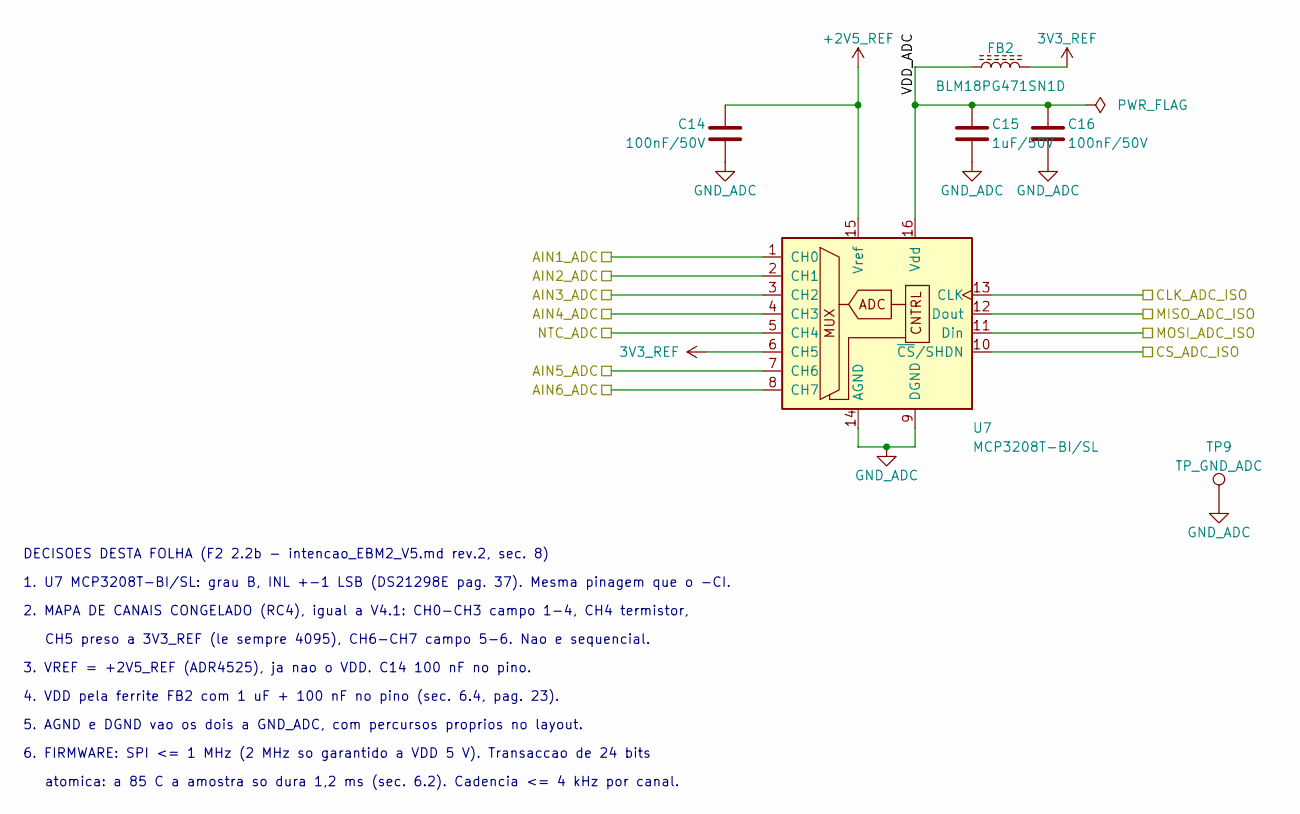
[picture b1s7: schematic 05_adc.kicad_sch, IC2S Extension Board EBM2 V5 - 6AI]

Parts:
C14, C16: 100nF/50V; 0603C; MPN C1608X7R1H104K080AA
C15: 1uF/50V; 0603C; MPN C1608X7R1H105K080AB
FB2: BLM18PG471SN1D; 0603FB; MPN BLM18PG471SN1D
TP9: TP_GND_ADC; TestPad_Via
U7: MCP3208T-BI/SL; SOIC16; MPN MCP3208T-BI/SL

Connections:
3V3_REF: FB2.2, U7.6 (CH5); also elsewhere on the board
+2V5_REF: C14.1, U7.15 (Vref); also elsewhere on the board
/4 Barreira digital/CLK_ADC_ISO: U7.13 (CLK); also elsewhere on the board
/4 Barreira digital/CS_ADC_ISO: U7.10 (~CS/SHDN); also elsewhere on the board
/4 Barreira digital/MISO_ADC_ISO: U7.12 (Dout); also elsewhere on the board
/4 Barreira digital/MOSI_ADC_ISO: U7.11 (Din); also elsewhere on the board
/5 ADC/AIN1_ADC: U7.1 (CH0); also elsewhere on the board
/5 ADC/AIN2_ADC: U7.2 (CH1); also elsewhere on the board
/5 ADC/AIN3_ADC: U7.3 (CH2); also elsewhere on the board
/5 ADC/AIN4_ADC: U7.4 (CH3); also elsewhere on the board
/5 ADC/AIN5_ADC: U7.7 (CH6); also elsewhere on the board
/5 ADC/AIN6_ADC: U7.8 (CH7); also elsewhere on the board
/5 ADC/NTC_ADC: U7.5 (CH4); also elsewhere on the board
/5 ADC/VDD_ADC: C15.1, C16.1, FB2.1, U7.16 (Vdd)
GND_ADC: C14.2, C15.2, C16.2, TP9.1, U7.9 (DGND), U7.14 (AGND); also elsewhere on the board

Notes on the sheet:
DECISOES DESTA FOLHA (F2 2.2b - intencao_EBM2_V5.md rev.2, sec. 8)
1. U7 MCP3208T-BI/SL: grau B, INL +-1 LSB (DS21298E pag. 37). Mesma pinagem que o -CI.
2. MAPA DE CANAIS CONGELADO (RC4), igual a V4.1: CH0-CH3 campo 1-4, CH4 termistor,
CH5 preso a 3V3_REF (le sempre 4095), CH6-CH7 campo 5-6. Nao e sequencial.
3. VREF = +2V5_REF (ADR4525), ja nao o VDD. C14 100 nF no pino.
4. VDD pela ferrite FB2 com 1 uF + 100 nF no pino (sec. 6.4, pag. 23).
5. AGND e DGND vao os dois a GND_ADC, com percursos proprios no layout.
6. FIRMWARE: SPI <= 1 MHz (2 MHz so garantido a VDD 5 V). Transaccao de 24 bits
atomica: a 85 C a amostra so dura 1,2 ms (sec. 6.2). Cadencia <= 4 kHz por canal.
